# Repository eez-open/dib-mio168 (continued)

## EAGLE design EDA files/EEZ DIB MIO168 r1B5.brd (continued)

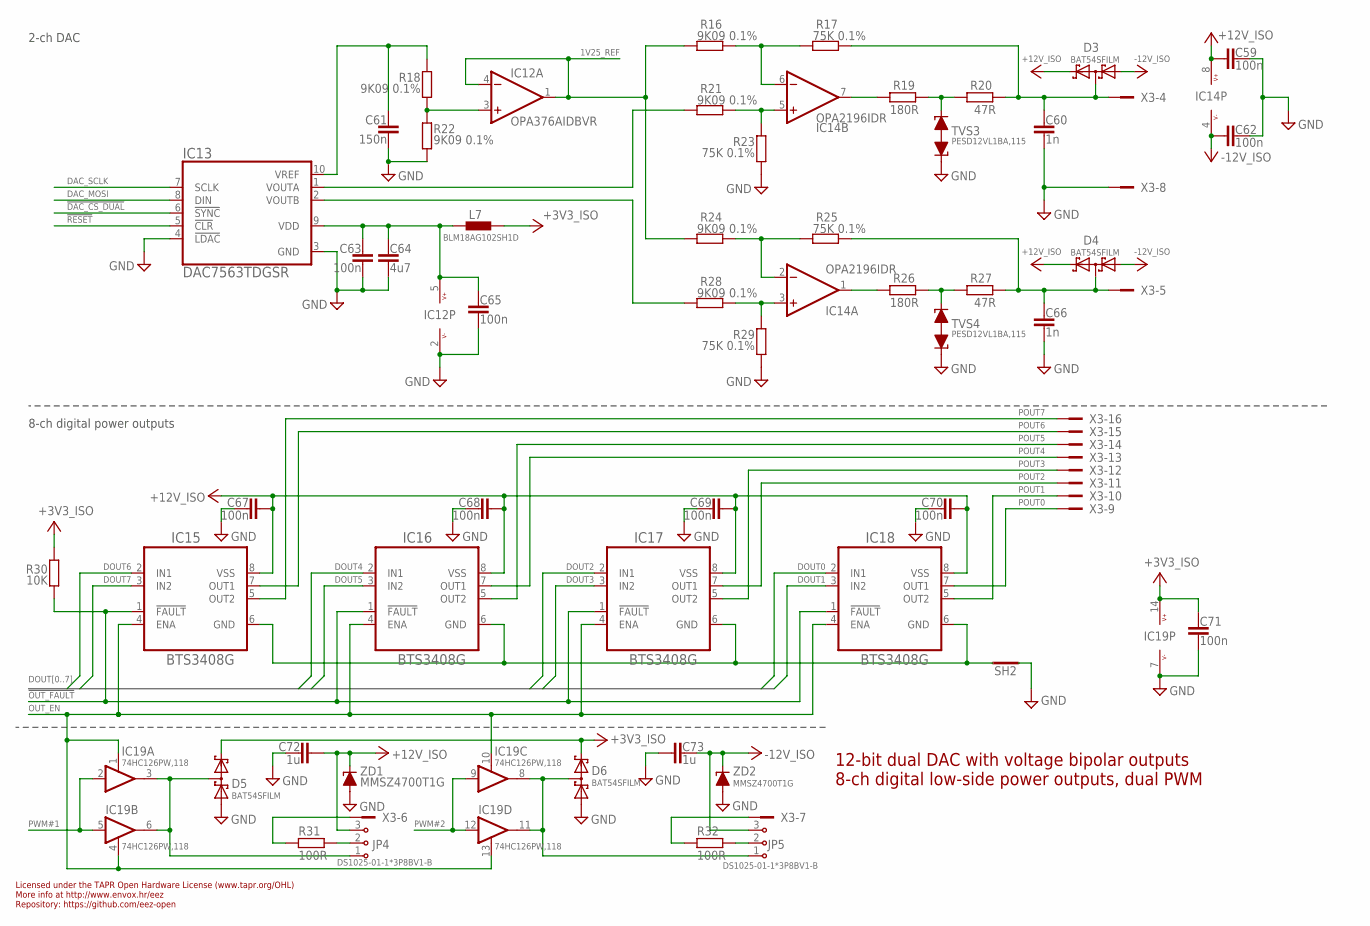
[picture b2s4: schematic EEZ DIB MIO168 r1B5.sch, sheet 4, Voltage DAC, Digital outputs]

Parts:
C59, C62, C63, C65, C67, C68, C69, C70, C71: 100n; C0603
C60, C66: 1n; C0805
C61: 150n; C0805
C64: 4u7; C0805
C72, C73: 1u; C0805
D3, D4, D5, D6: BAT54SFILM; SOT23
IC12: OPA376AIDBVR; DBV5
IC13: DAC7563TDGSR; DGS10
IC14: OPA2196IDR; SOIC127P600X173-8N
IC15, IC16, IC17, IC18: BTS3408G; SOIC127P600X173-8N
IC19: 74HC126PW,118; PW14
JP4, JP5: DS1025-01-1*3P8BV1-B; ZL303-03P
L7: BLM18AG102SH1D; BEAD0603
R16, R18, R21, R22, R24, R28: 9K09 0.1%; R0805
R17, R23, R25, R29: 75K 0.1%; R0805
R19, R26: 180R; R0805
R20, R27: 47R; R0805
R30: 10K; R0805
R31, R32: 100R; R0805
SH2: SHORTNOHOLE; SHORT_NOHOLE
TVS3, TVS4: PESD12VL1BA,115; SOD323-BIDIR
X3: 691327310016
ZD1, ZD2: MMSZ4700T1G; SOD123

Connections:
1V25_REF: IC12.1 (OUT), IC12.4 (-IN), R16.2, R24.2; also elsewhere on the board
2V5_REF: C61.2, IC13.10 (VREF), R18.1
!DAC_CS_DUAL: IC13.6 (!SYNC); also elsewhere on the board
!OUT_FAULT: IC15.1 (!FAULT), IC16.1 (!FAULT), IC17.1 (!FAULT), IC18.1 (!FAULT), R30.2; also elsewhere on the board
!RESET: IC13.5 (!CLR); also elsewhere on the board
+3V3_ISO: C71.2, D5.2 (C2), D6.2 (C2), IC19.14 (V+), L7.P$2 (2), R30.1; also elsewhere on the board
+12V_ISO: C59.1, C67.2, C68.2, C69.2, C70.2, C72.1, D3.2 (C2), D4.2 (C2), IC14.8 (V+), IC15.8 (VSS), IC16.8 (VSS), IC17.8 (VSS), IC18.8 (VSS), JP4.3, ZD1.C; also elsewhere on the board
-12V_ISO: C62.1, C73.1, D3.1 (A1), D4.1 (A1), IC14.4 (V-), JP5.3, ZD2.C; also elsewhere on the board
DAC_MOSI: IC13.8 (DIN); also elsewhere on the board
DAC_SCLK: IC13.7 (SCLK); also elsewhere on the board
DOUT0: IC18.2 (IN1); also elsewhere on the board
DOUT1: IC18.3 (IN2); also elsewhere on the board
DOUT2: IC17.2 (IN1); also elsewhere on the board
DOUT3: IC17.3 (IN2); also elsewhere on the board
DOUT4: IC16.2 (IN1); also elsewhere on the board
DOUT5: IC16.3 (IN2); also elsewhere on the board
DOUT6: IC15.2 (IN1); also elsewhere on the board
DOUT7: IC15.3 (IN2); also elsewhere on the board
GND: C59.2, C60.2, C61.1, C62.2, C63.2, C64.1, C65.2, C66.2, C67.1, C68.1, C69.1, C70.1, C71.1, C72.2, C73.2, D5.1 (A1), D6.1 (A1), IC12.2 (V-), IC13.3 (GND), IC13.4 (!LDAC), IC19.7 (V-), R22.2, R23.2, R29.2, SH2.1 (GND_A), TVS3.C1 (1), TVS4.C1 (1), X3.8, ZD1.A, ZD2.A; also elsewhere on the board
ISET1: R19.2, R20.1, TVS3.C2 (2)
ISET2: R26.2, R27.1, TVS4.C2 (2)
unnamed: IC15.6 (GND), IC16.6 (GND), IC17.6 (GND), IC18.6 (GND), SH2.2 (GND_B)
unnamed: JP4.2, R31.1
unnamed: R31.2, X3.6
unnamed: R32.2, X3.7
unnamed: JP5.2, R32.1
unnamed: IC14.5 (+IN), R21.1, R23.1
unnamed: IC14.6 (-IN), R16.1, R17.2
unnamed: IC14.7 (OUT), R19.1
unnamed: IC14.3 (+IN), R28.1, R29.1
unnamed: IC14.2 (-IN), R24.1, R25.2
unnamed: IC14.1 (OUT), R26.1
unnamed: IC12.3 (+IN), R18.2, R22.1
unnamed: IC13.1 (VOUTA), R21.2
unnamed: IC13.2 (VOUTB), R28.2
unnamed: C63.1, C64.2, C65.1, IC12.5 (V+), IC13.9 (VDD), L7.P$1 (1)
unnamed: C66.1, D4.3 (C1A2), R25.1, R27.2, X3.5
unnamed: C60.1, D3.3 (C1A2), R17.1, R20.2, X3.4
unnamed: D5.3 (C1A2), IC19.3 (O), IC19.6 (O), JP4.1
unnamed: D6.3 (C1A2), IC19.8 (O), IC19.11 (O), JP5.1
OUT_EN: IC15.4 (ENA), IC16.4 (ENA), IC17.4 (ENA), IC18.4 (ENA), IC19.1 (EN), IC19.4 (EN), IC19.10 (EN), IC19.13 (EN); also elsewhere on the board
POUT0: IC18.7 (OUT1), X3.9
POUT1: IC18.5 (OUT2), X3.10
POUT2: IC17.7 (OUT1), X3.11
POUT3: IC17.5 (OUT2), X3.12
POUT4: IC16.7 (OUT1), X3.13
POUT5: IC16.5 (OUT2), X3.14
POUT6: IC15.7 (OUT1), X3.15
POUT7: IC15.5 (OUT2), X3.16
PWM#1: IC19.2 (I), IC19.5 (I); also elsewhere on the board
PWM#2: IC19.9 (I), IC19.12 (I); also elsewhere on the board

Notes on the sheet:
Licensed under the TAPR Open Hardware License (www.tapr.org/OHL)
Repository: https://github.com/eez-open
More info at http://www.envox.hr/eez
12-bit dual DAC with voltage bipolar outputs 8-ch digital low-side power outputs, dual PWM
8-ch digital power outputs
2-ch DAC

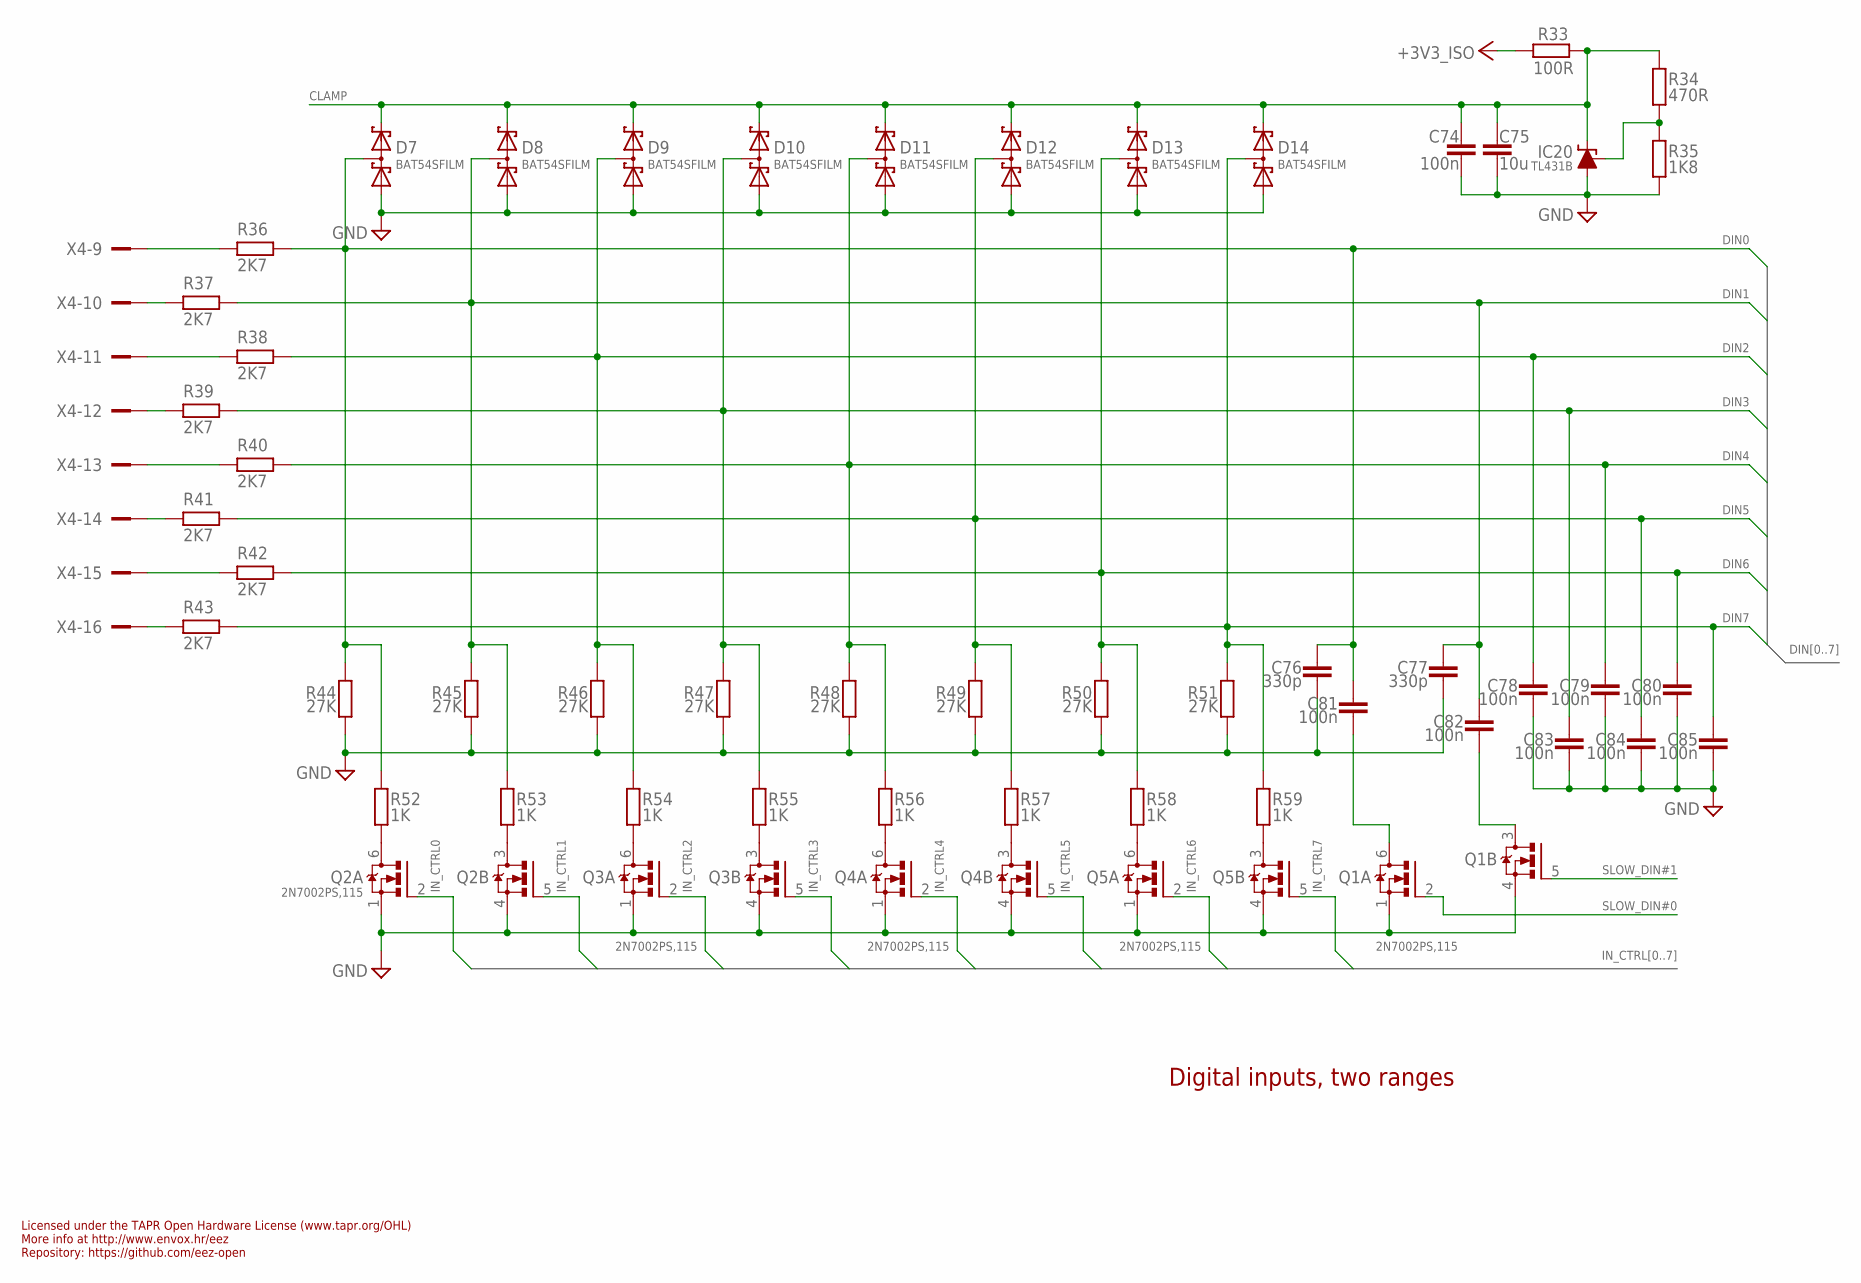
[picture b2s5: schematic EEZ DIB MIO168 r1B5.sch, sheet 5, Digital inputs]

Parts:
C74, C78, C79, C80, C81, C82, C83, C84, C85: 100n; C0603
C75: 10u; C1206
C76, C77: 330p; C0805
D7, D8, D9, D10, D11, D12, D13, D14: BAT54SFILM; SOT23
IC20: TL431B; SOT103P240X110-3N
Q1, Q2, Q3, Q4, Q5: 2N7002PS,115; SC88
R33: 100R; R0805
R34: 470R; R0805
R35: 1K8; R0805
R36, R37, R38, R39, R40, R41, R42, R43: 2K7; R1206
R44, R45, R46, R47, R48, R49, R50, R51: 27K; R0805
R52, R53, R54, R55, R56, R57, R58, R59: 1K; R0805
X4: 691327310016

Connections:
+3V3_ISO: R33.1; also elsewhere on the board
CLAMP: C74.1, C75.1, D7.2 (C2), D8.2 (C2), D9.2 (C2), D10.2 (C2), D11.2 (C2), D12.2 (C2), D13.2 (C2), D14.2 (C2), IC20.1 (C), R33.2, R34.1
DIN0: C76.1, C81.1, D7.3 (C1A2), R36.2, R44.2, R52.1; also elsewhere on the board
DIN1: C77.1, C82.1, D8.3 (C1A2), R37.2, R45.2, R53.1; also elsewhere on the board
DIN2: C78.1, D9.3 (C1A2), R38.2, R46.2, R54.1; also elsewhere on the board
DIN3: C83.1, D10.3 (C1A2), R39.2, R47.2, R55.1; also elsewhere on the board
DIN4: C79.1, D11.3 (C1A2), R40.2, R48.2, R56.1; also elsewhere on the board
DIN5: C84.1, D12.3 (C1A2), R41.2, R49.2, R57.1; also elsewhere on the board
DIN6: C80.1, D13.3 (C1A2), R42.2, R50.2, R58.1; also elsewhere on the board
DIN7: C85.1, D14.3 (C1A2), R43.2, R51.2, R59.1; also elsewhere on the board
GND: C74.2, C75.2, C76.2, C77.2, C78.2, C79.2, C80.2, C83.2, C84.2, C85.2, D7.1 (A1), D8.1 (A1), D9.1 (A1), D10.1 (A1), D11.1 (A1), D12.1 (A1), D13.1 (A1), D14.1 (A1), IC20.3 (A), Q1.1 (S), Q1.4 (S), Q2.1 (S), Q2.4 (S), Q3.1 (S), Q3.4 (S), Q4.1 (S), Q4.4 (S), Q5.1 (S), Q5.4 (S), R35.2, R44.1, R45.1, R46.1, R47.1, R48.1, R49.1, R50.1, R51.1; also elsewhere on the board
IN_CTRL0: Q2.2 (G); also elsewhere on the board
IN_CTRL1: Q2.5 (G); also elsewhere on the board
IN_CTRL2: Q3.2 (G); also elsewhere on the board
IN_CTRL3: Q3.5 (G); also elsewhere on the board
IN_CTRL4: Q4.2 (G); also elsewhere on the board
IN_CTRL5: Q4.5 (G); also elsewhere on the board
IN_CTRL6: Q5.2 (G); also elsewhere on the board
IN_CTRL7: Q5.5 (G); also elsewhere on the board
unnamed: IC20.2 (R), R34.2, R35.1
unnamed: Q2.6 (D), R52.2
unnamed: Q2.3 (D), R53.2
unnamed: Q3.6 (D), R54.2
unnamed: Q3.3 (D), R55.2
unnamed: R37.1, X4.10
unnamed: Q4.6 (D), R56.2
unnamed: Q4.3 (D), R57.2
unnamed: Q5.6 (D), R58.2
unnamed: Q5.3 (D), R59.2
unnamed: C81.2, Q1.6 (D)
unnamed: R36.1, X4.9
unnamed: R38.1, X4.11
unnamed: R39.1, X4.12
unnamed: C82.2, Q1.3 (D)
unnamed: R40.1, X4.13
unnamed: R42.1, X4.15
unnamed: R43.1, X4.16
unnamed: R41.1, X4.14
SLOW_DIN#0: Q1.2 (G); also elsewhere on the board
SLOW_DIN#1: Q1.5 (G); also elsewhere on the board

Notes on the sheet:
Licensed under the TAPR Open Hardware License (www.tapr.org/OHL)
Repository: https://github.com/eez-open
More info at http://www.envox.hr/eez
Digital inputs, two ranges

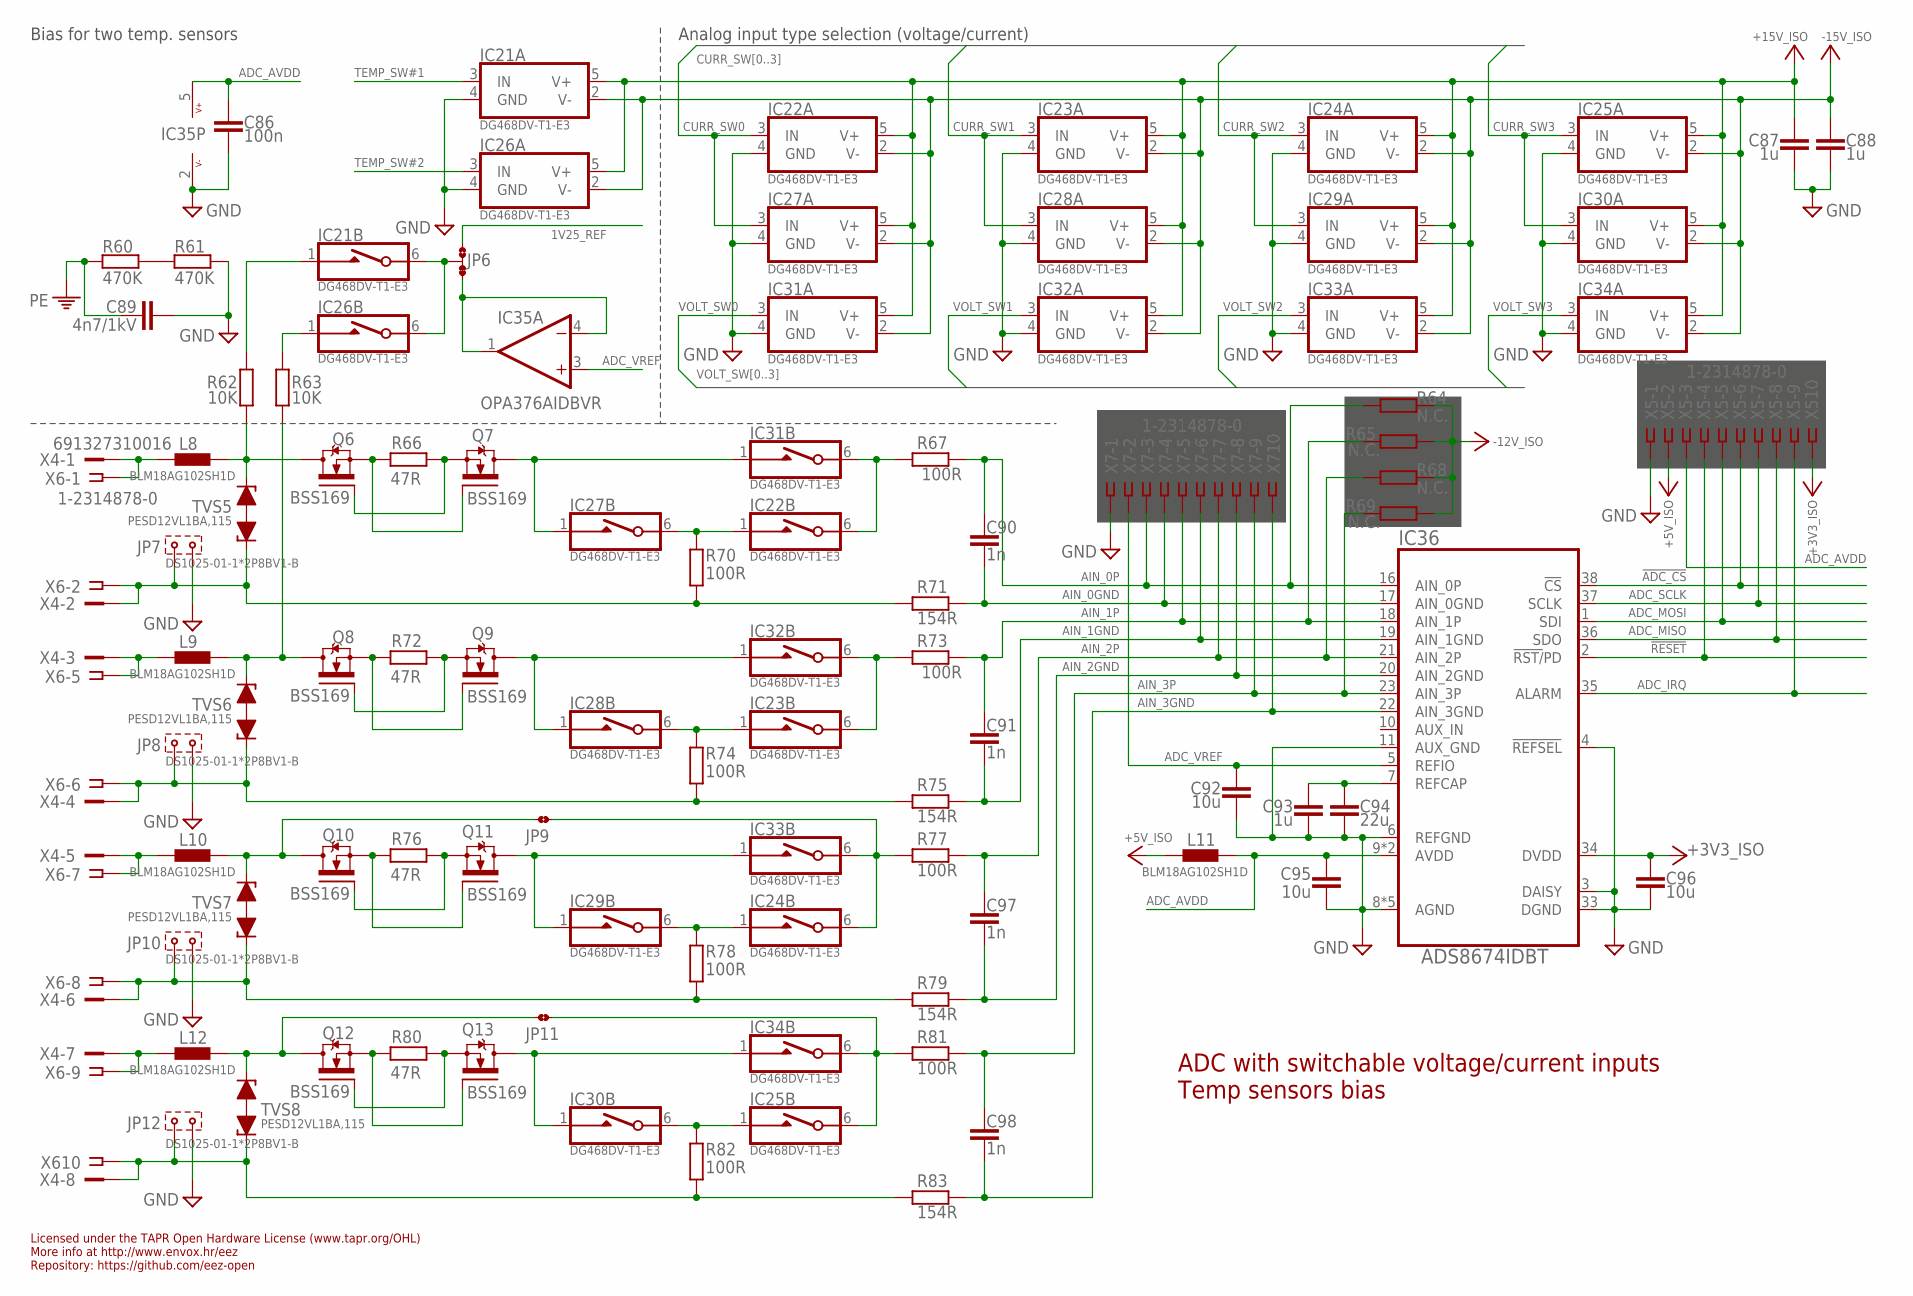
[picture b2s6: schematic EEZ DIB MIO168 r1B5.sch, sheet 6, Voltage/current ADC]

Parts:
C86: 100n; C0603
C87, C88, C93: 1u; C0805
C89: 4n7/1kV; C1812
C90, C91, C97, C98: 1n; C0805
C92, C95, C96: 10u; C1206
C94: 22u; C1206
IC21, IC22, IC23, IC24, IC25, IC26, IC27, IC28, IC29, IC30, IC31, IC32, IC33, IC34: DG468DV-T1-E3; DG6_TSOP6
IC35: OPA376AIDBVR; DBV5
IC36: ADS8674IDBT; DBT38
JP6: JP3-CUT-0805-ROTATED; JP3-0805-CUT2
JP7, JP8, JP10, JP12: DS1025-01-1*2P8BV1-B; 2MM-2
JP9, JP11: JP2-CUT-0805; R_0805
L8, L9, L10, L11, L12: BLM18AG102SH1D; BEAD0603
Q6, Q7, Q8, Q9, Q10, Q11, Q12, Q13: BSS169; SOT103P240X110-3N
R60, R61: 470K; R1206
R62, R63: 10K; R0805
R64, R65, R68, R69: N.C.; R0805
R66, R72, R76, R80: 47R; R0805
R67, R70, R73, R74, R77, R78, R81, R82: 100R; R0805
R71, R75, R79, R83: 154R; R0805
TVS5, TVS6, TVS7, TVS8: PESD12VL1BA,115; SOD323-BIDIR
X4: 691327310016
X5, X6, X7: 1-2314878-0

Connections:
1V25_REF: JP6.NO; also elsewhere on the board
!ADC_CS: IC36.38 (!CS), X5.6; also elsewhere on the board
!RESET: IC36.2 (!RST/!PD), X5.4; also elsewhere on the board
+3V3_ISO: C96.2, IC36.34 (DVDD), X5.10; also elsewhere on the board
+5V_ISO: L11.P$1 (1), X5.2; also elsewhere on the board
+15V_ISO: C87.1, IC21.5 (V+), IC22.5 (V+), IC23.5 (V+), IC24.5 (V+), IC25.5 (V+), IC26.5 (V+), IC27.5 (V+), IC28.5 (V+), IC29.5 (V+), IC30.5 (V+), IC31.5 (V+), IC32.5 (V+), IC33.5 (V+), IC34.5 (V+); also elsewhere on the board
-12V_ISO: R64.1, R65.1, R68.1, R69.1; also elsewhere on the board
-15V_ISO: C88.1, IC21.2 (V-), IC22.2 (V-), IC23.2 (V-), IC24.2 (V-), IC25.2 (V-), IC26.2 (V-), IC27.2 (V-), IC28.2 (V-), IC29.2 (V-), IC30.2 (V-), IC31.2 (V-), IC32.2 (V-), IC33.2 (V-), IC34.2 (V-); also elsewhere on the board
ADC_AVDD: C86.1, C95.2, IC35.5 (V+), IC36.9 (AVDD), IC36.30 (AVDD), L11.P$2 (2), X5.3
ADC_IRQ: IC36.35 (ALARM), X5.9; also elsewhere on the board
ADC_MISO: IC36.36 (SDO), X5.8; also elsewhere on the board
ADC_MOSI: IC36.1 (SDI), X5.5; also elsewhere on the board
ADC_SCLK: IC36.37 (SCLK), X5.7; also elsewhere on the board
ADC_VREF: C92.2, IC35.3 (+IN), IC36.5 (REFIO), X7.2
AGND2: JP8.1, R74.1, R75.1, TVS6.C1 (1), X4.4, X6.6
AGND4: JP12.1, R82.1, R83.1, TVS8.C1 (1), X4.8, X6.10
AIN0: L8.P$2 (2), Q6.3 (D), R62.2, TVS5.C2 (2)
AIN1: L9.P$2 (2), Q8.3 (D), R63.2, TVS6.C2 (2)
AIN_0GND: C90.1, IC36.17 (AIN_0GND), R71.2, X7.4
AIN_0P: C90.2, IC36.16 (AIN_0P), R64.2, R67.2, X7.3
AIN_1GND: C91.1, IC36.19 (AIN_1GND), R75.2, X7.6
AIN_1P: C91.2, IC36.18 (AIN_1P), R65.2, R73.2, X7.5
AIN_2GND: C97.1, IC36.20 (AIN_2GND), R79.2, X7.8
AIN_2P: C97.2, IC36.21 (AIN_2P), R68.2, R77.2, X7.7
AIN_3GND: C98.1, IC36.22 (AIN_3GND), R83.2, X7.10
AIN_3P: C98.2, IC36.23 (AIN_3P), R69.2, R81.2, X7.9
CURR_SW0: IC22.3 (IN), IC27.3 (IN); also elsewhere on the board
CURR_SW1: IC23.3 (IN), IC28.3 (IN); also elsewhere on the board
CURR_SW2: IC24.3 (IN), IC29.3 (IN); also elsewhere on the board
CURR_SW3: IC25.3 (IN), IC30.3 (IN); also elsewhere on the board
GND: C86.2, C87.2, C88.2, C89.2, C92.1, C93.1, C94.1, C95.1, C96.1, IC21.4 (GND), IC22.4 (GND), IC23.4 (GND), IC24.4 (GND), IC25.4 (GND), IC26.4 (GND), IC27.4 (GND), IC28.4 (GND), IC29.4 (GND), IC30.4 (GND), IC31.4 (GND), IC32.4 (GND), IC33.4 (GND), IC34.4 (GND), IC35.2 (V-), IC36.3 (DAISY), IC36.4 (!REFSEL), IC36.6 (REFGND), IC36.8 (AGND), IC36.11 (AUX_GND), IC36.28 (AGND), IC36.29 (AGND), IC36.31 (AGND), IC36.32 (AGND), IC36.33 (DGND), JP7.2, JP8.2, JP10.2, JP12.2, R61.2, X5.1, X7.1; also elsewhere on the board
unnamed: Q12.1 (G), Q13.2 (S), R80.1
unnamed: JP10.1, R78.1, R79.1, TVS7.C1 (1), X4.6, X6.8
unnamed: Q12.2 (S), Q13.1 (G), R80.2
unnamed: IC25.1 (NO), IC30.6 (COM), R82.2
unnamed: IC21.6 (COM), IC26.6 (COM), JP6.COM
unnamed: R60.2, R61.1
unnamed: IC25.6 (COM), IC34.6 (COM), JP11.2, R81.1
unnamed: IC30.1 (NO), IC34.1 (NO), Q13.3 (D)
unnamed: IC35.1 (OUT), IC35.4 (-IN), JP6.NC
unnamed: Q8.1 (G), Q9.2 (S), R72.1
unnamed: Q8.2 (S), Q9.1 (G), R72.2
unnamed: C93.2, C94.2, IC36.7 (REFCAP)
unnamed: JP7.1, R70.1, R71.1, TVS5.C1 (1), X4.2, X6.2
unnamed: IC23.1 (NO), IC28.6 (COM), R74.2
unnamed: IC23.6 (COM), IC32.6 (COM), R73.1
unnamed: IC28.1 (NO), IC32.1 (NO), Q9.3 (D)
unnamed: Q10.1 (G), Q11.2 (S), R76.1
unnamed: Q6.1 (G), Q7.2 (S), R66.1
unnamed: Q10.2 (S), Q11.1 (G), R76.2
unnamed: IC24.1 (NO), IC29.6 (COM), R78.2
unnamed: Q6.2 (S), Q7.1 (G), R66.2
unnamed: IC24.6 (COM), IC33.6 (COM), JP9.2, R77.1
unnamed: IC29.1 (NO), IC33.1 (NO), Q11.3 (D)
unnamed: IC22.1 (NO), IC27.6 (COM), R70.2
unnamed: L8.P$1 (1), X4.1, X6.1
unnamed: IC22.6 (COM), IC31.6 (COM), R67.1
unnamed: L9.P$1 (1), X4.3, X6.5
unnamed: L10.P$1 (1), X4.5, X6.7
unnamed: IC27.1 (NO), IC31.1 (NO), Q7.3 (D)
unnamed: L12.P$1 (1), X4.7, X6.9
unnamed: IC21.1 (NO), R62.1
unnamed: IC26.1 (NO), R63.1
unnamed: JP9.1, L10.P$2 (2), Q10.3 (D), TVS7.C2 (2)
unnamed: JP11.1, L12.P$2 (2), Q12.3 (D), TVS8.C2 (2)
PE: C89.1, R60.1; also elsewhere on the board
TEMP_SW#1: IC21.3 (IN); also elsewhere on the board
TEMP_SW#2: IC26.3 (IN); also elsewhere on the board
VOLT_SW0: IC31.3 (IN); also elsewhere on the board
VOLT_SW1: IC32.3 (IN); also elsewhere on the board
VOLT_SW2: IC33.3 (IN); also elsewhere on the board
VOLT_SW3: IC34.3 (IN); also elsewhere on the board

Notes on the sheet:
Licensed under the TAPR Open Hardware License (www.tapr.org/OHL)
Repository: https://github.com/eez-open
More info at http://www.envox.hr/eez
ADC with switchable voltage/current inputs Temp sensors bias
Bias for two temp. sensors
Analog input type selection (voltage/current)

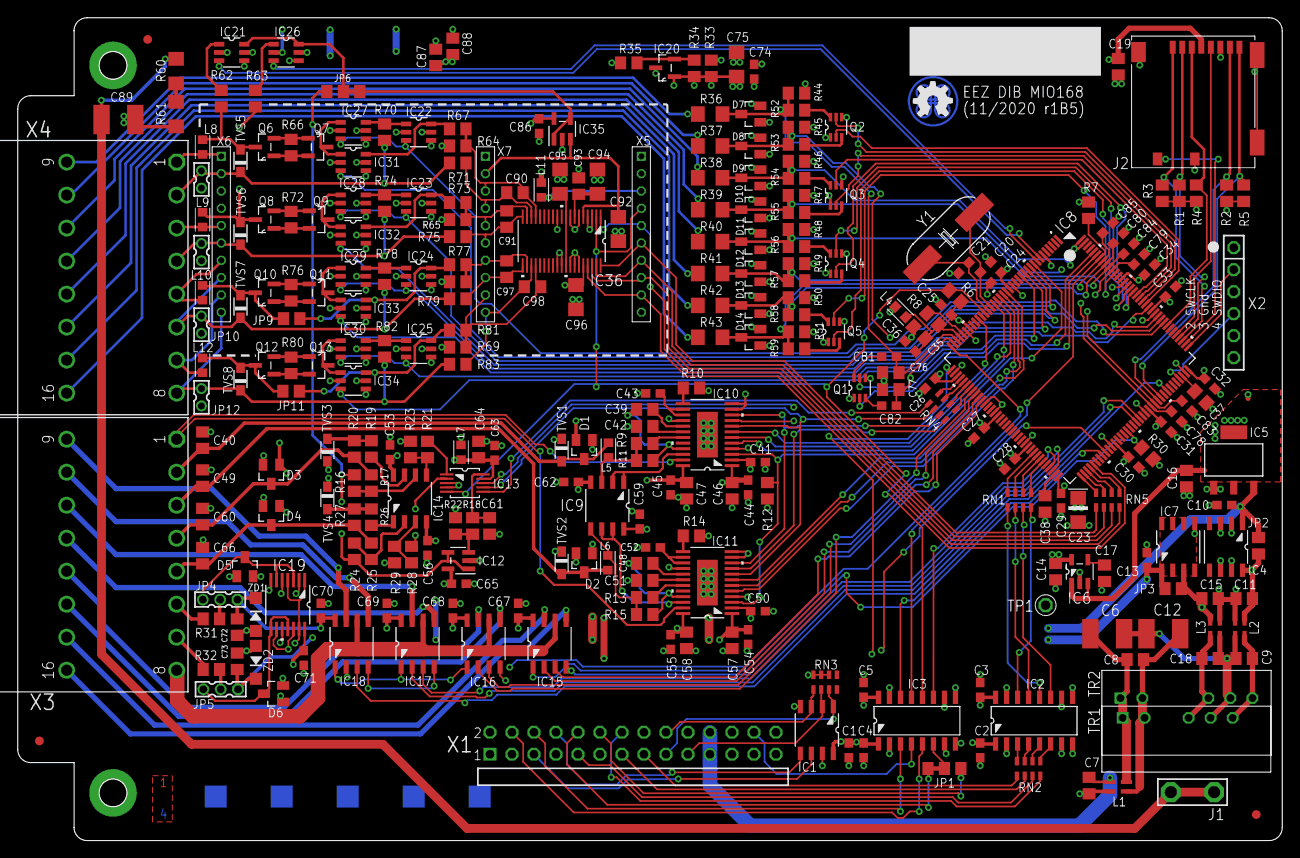
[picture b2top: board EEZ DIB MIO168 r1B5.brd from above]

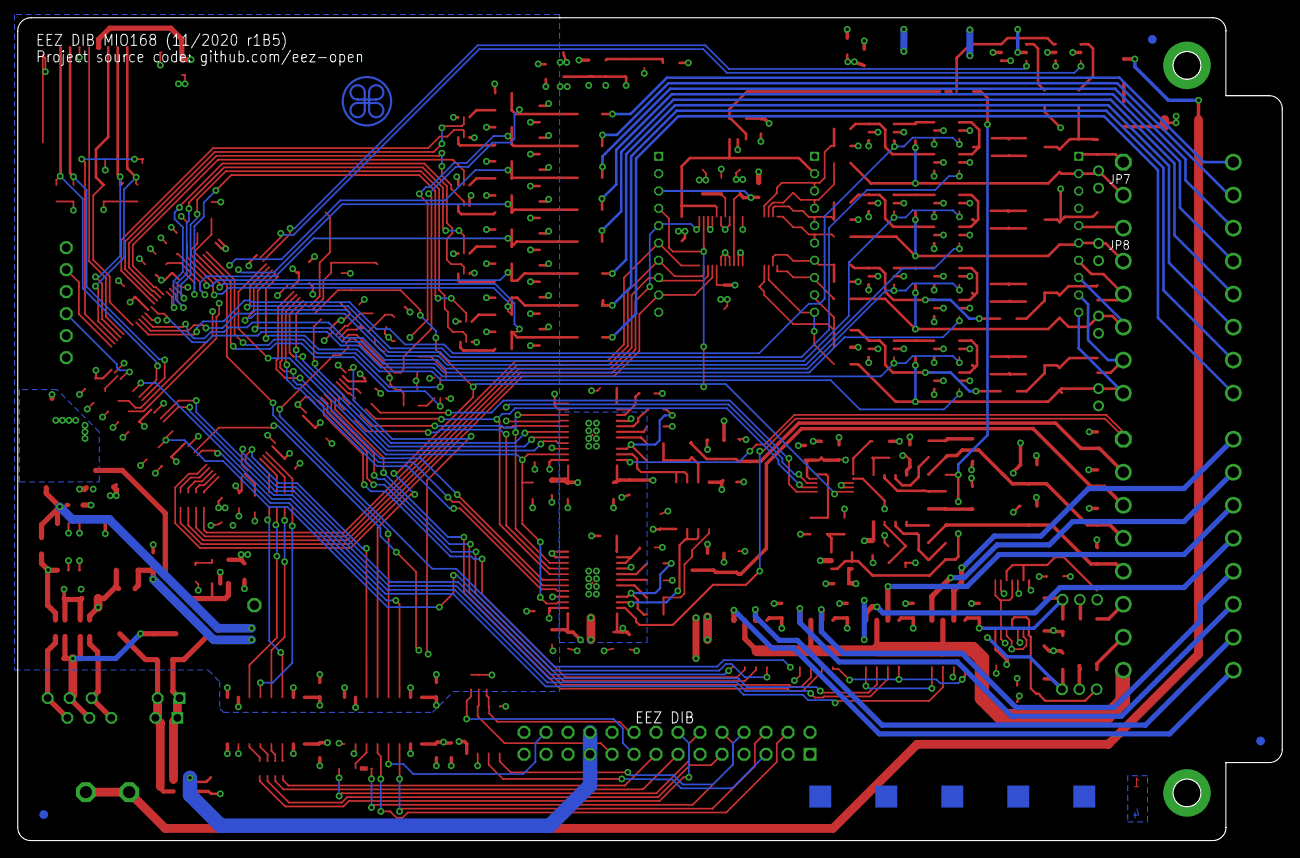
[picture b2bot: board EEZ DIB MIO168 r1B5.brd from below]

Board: 4 copper layers, 146.0 x 95.0 mm, 303 parts (2 on the bottom side), 245 nets.

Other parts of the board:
EEZ_SIGNATURE: SIGNATURESMALL; SIGNATURE_5MM

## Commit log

2020-03-09 IC36 name, value added
2020-03-10 BOM added
2020-03-10 readme.md update
2020-03-10 PWM outputs clamp fix
2020-03-10 Vref selection for NTC bias (JP3)
2020-03-13 schematics PDF update
2020-03-14 Changes suggested by @jbb
2020-03-15 2N7002PS package fixed
2020-03-15 PCB preview update
2020-03-19 front panel connectors position adjusted
2020-04-06 #1 fixed
2020-05-05 Slave SPI moved to SPI4
2020-05-18 prototype picture
2020-06-12 IRQ selection jumper
2020-07-08 r1B2 picture update
2020-08-27 Connectors for piggyback, GND and PWM outputs jumpers
2020-09-09 MCU Vdd update
2020-10-11 #4, BOM update
2020-10-17 ZD1, ZD2 added
2020-10-31 PWM outputs pin rearrangement
2020-10-31 swap DOUT0 and DOUT1
2021-01-22 r2B4 version
2021-01-31 PCB ID added
2021-02-07 BOM update
2021-03-29 r2B5, ADIB switcing
2021-03-29 r2B5 .ioc
2021-03-29 BOM, .ioc update
2021-06-04 DIN3 PCB correction
2021-10-08 OSHWA UID
2024-01-19 #6, #7, r1B3 (KiCad)
2024-01-20 PCB preview correction
